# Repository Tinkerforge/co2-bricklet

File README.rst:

CO2 Bricklet
============

This repository contains the firmware source code and the hardware design
files. The documentation generator configs can be found at
https://github.com/Tinkerforge/generators

Repository Content
------------------

software/:
 * examples/: Examples for all supported languages
 * build/: Compiled files
 * src/: Source code of firmware
 * Makefile: Makefile to build project

hardware/:
 * Contains KiCad project files and additionally schematics as PDF

datasheets/:
 * Contains datasheets for sensors and complex ICs that are used

Hardware
--------

The hardware is designed with the open source EDA Suite KiCad
(http://www.kicad.org). Before you are able to open the files,
you have to install the Tinkerforge kicad-libraries
(https://github.com/Tinkerforge/kicad-libraries). You can either clone
them directly in hardware/ or clone them in a separate folder and
symlink them into hardware/
(ln -s kicad_path/kicad-libraries project_path/hardware). After that you
can open the .pro file in hardware/ with KiCad and from there view and
modify the schematics and the PCB layout.

Software
--------

If you want to do your own Brick/Bricklet firmware development we highly
recommend that you use our build environment setup script and read the
tutorial (https://www.tinkerforge.com/en/doc/Tutorials/Tutorial_Build_Environment/Tutorial.html).

To compile the C code we recommend you to install the newest GNU Arm Embedded
Toolchain (https://launchpad.net/gcc-arm-embedded/+download).
You also need to install bricklib (https://github.com/Tinkerforge/bricklib)
and brickletlib (https://github.com/Tinkerforge/brickletlib).

You can either clone it directly in software/src/ or clone it in a
separate folder and symlink it into software/src/
(ln -s bricklib_path/bricklib project_path/software/src/ and
ln -s brickletlib_path/brickletlib project_path/software/src/).
Finally make sure to have CMake installed
(http://www.cmake.org/cmake/resources/software.html).

After that you can build the firmware by invoking make in software/.
The firmware (.bin) can then be found in software/build/ and uploaded
with brickv (click button "Flashing" on start screen).

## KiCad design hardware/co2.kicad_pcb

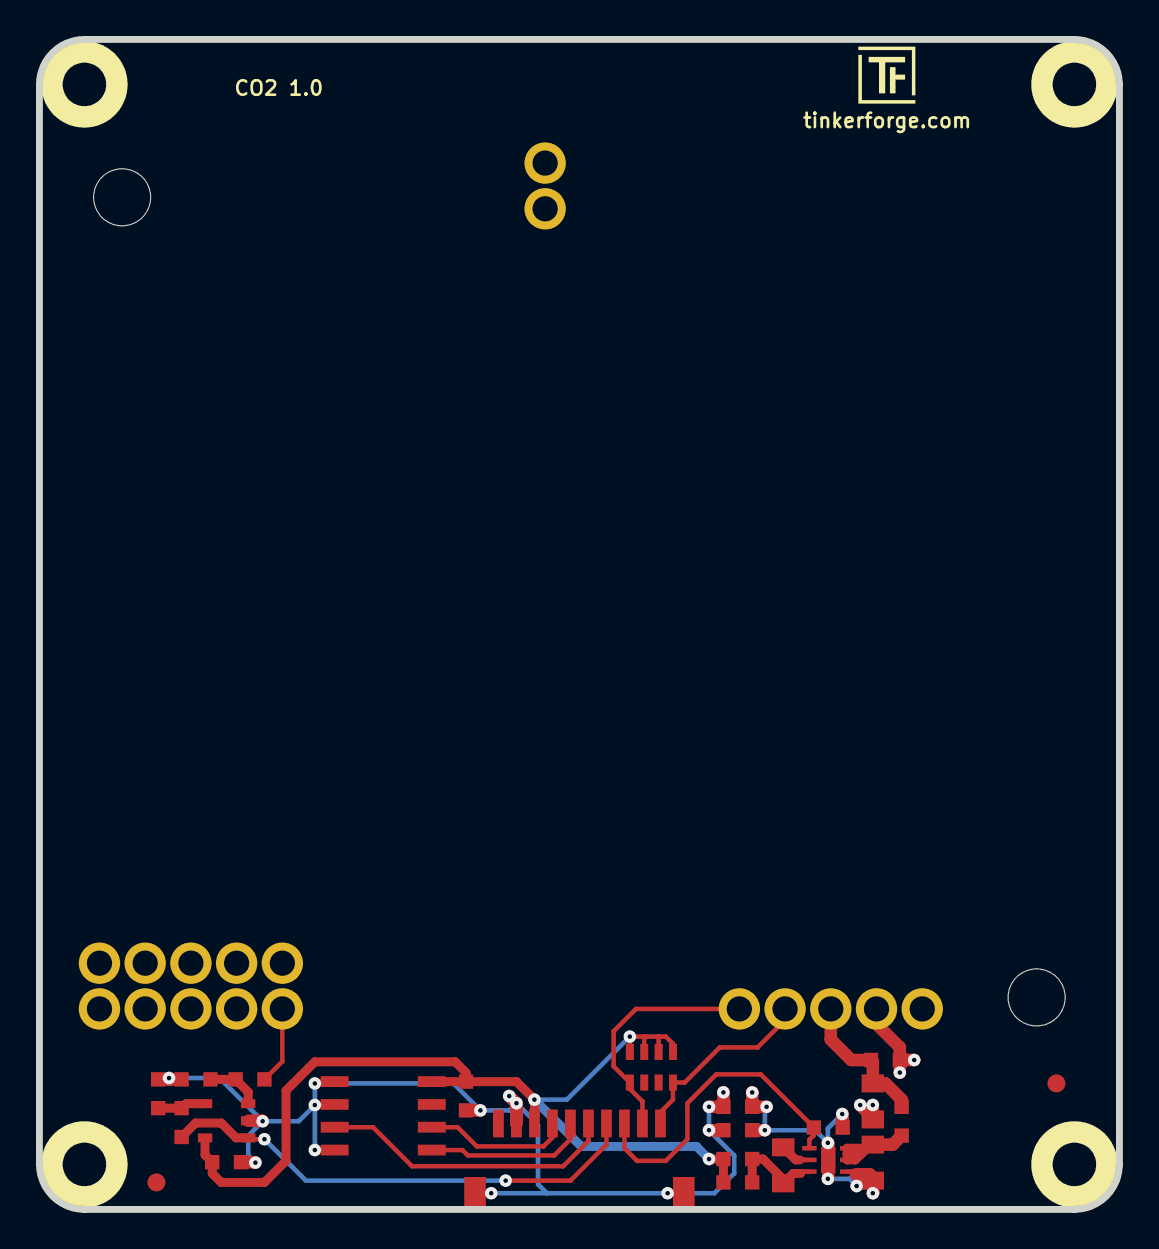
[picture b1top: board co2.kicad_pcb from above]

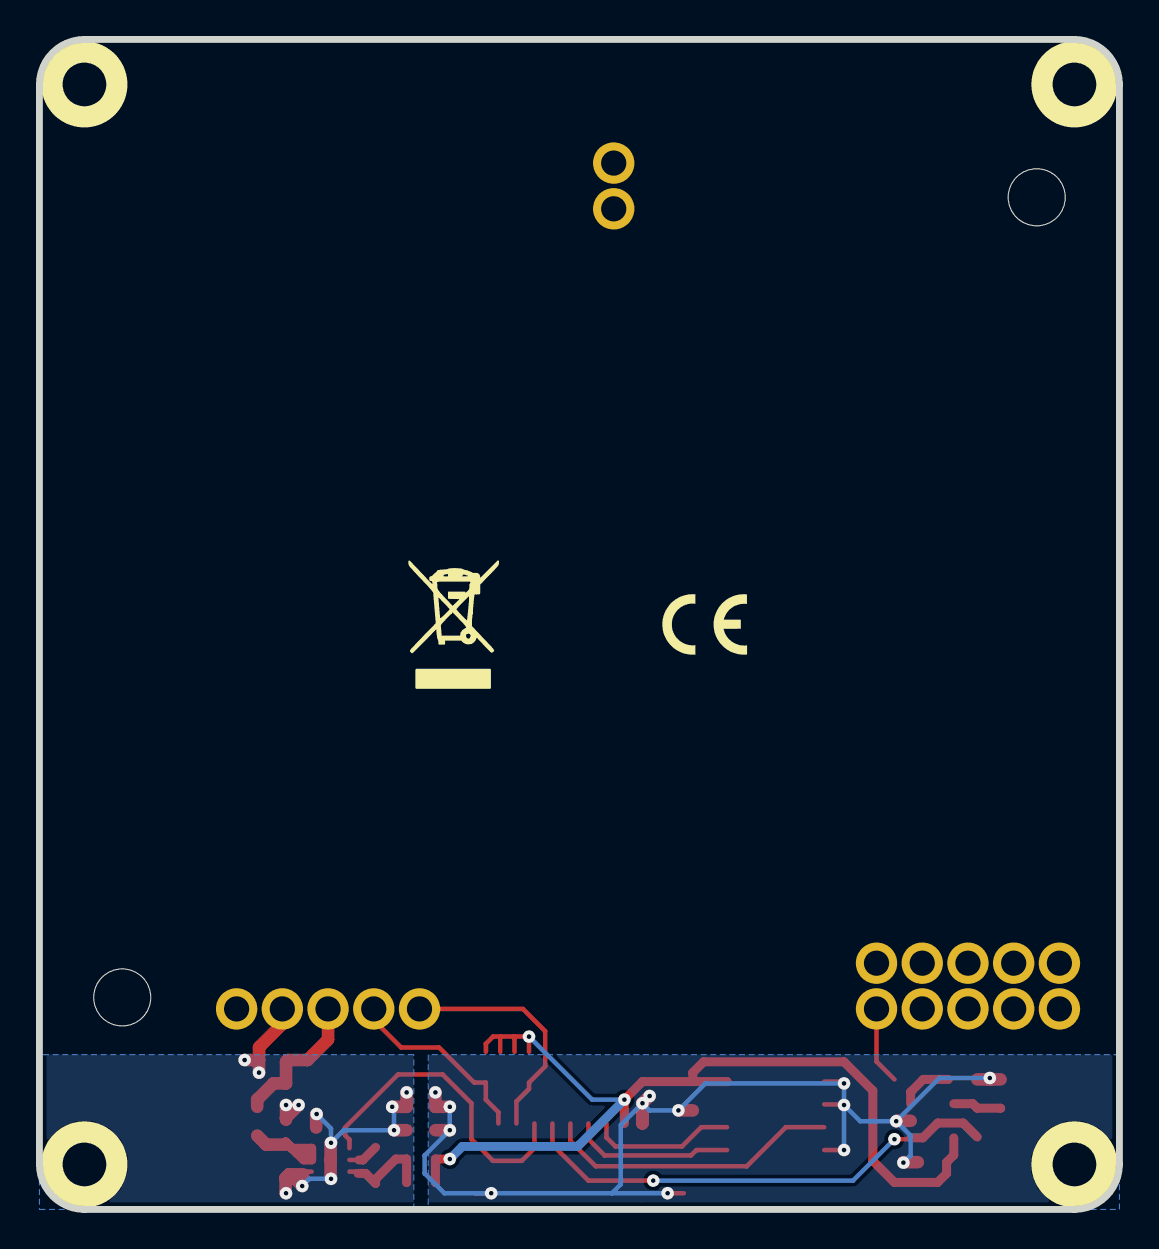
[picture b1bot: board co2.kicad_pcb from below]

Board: 2 copper layers, 60.0 x 65.0 mm, 30 parts (2 on the bottom side), 17 nets.

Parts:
C1, C2: 2.2µF; C0603
C3, C5, C7: 100nF; C0603
C4, C6: 4.7µF; C0805
Fiducial_Mark: VAL**; Fiducial_Mark
Fiducial_Mark#2: VAL**; Fiducial_Mark
L1, L4: INDUCT; C0603
L2: 0; C0603
L3: 1µH; C0805
P1: CON-SENSOR
R1: 10k; R0603
R2, R3: 3k; R0603
R4, R5: 3k9; R0603
RP1: 2k2; 4X0603
U1: M24C64; SOIC8
U2: FAN4860; UMLP_22
U3: TLV271; SOT23-5
U4: K30
U5, U6, U7, U8: DRILL; DRILL_NP
VAL: CE_5mm
VAL#2: WEEE_7mm_back; WEEE_7mm

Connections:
3V3: C1.1, C3.2, C5.2, L1.1, P1.3, RP1.1, RP1.2, RP1.3, RP1.4, U1.8, U3.5
+5V: C6.2, C7.2, L4.2, U4.3
AGND: C2.2, C4.2, C6.1, C7.1, L2.2, R1.2, U2.1, U2.EP, U4.2
EN: P1.8, R1.1, U2.4
GND: C1.2, C3.1, C5.1, L2.1, P1.2, P1.EP, R3.1, R4.1, U1.1, U1.2, U1.4, U3.2
unnamed: C2.1, L1.2, L3.1, U2.6
unnamed: C4.1, L4.1, U2.2, U2.3
unnamed: L3.2, U2.5
unnamed: P1.4, U1.6
unnamed: P1.5, U1.5
unnamed: P1.6, U1.3
unnamed: P1.7, R2.2, U3.1
unnamed: R2.1, R4.2, U3.4
unnamed: R3.2, R5.2, U3.3
unnamed: R5.1, U4.15
SCL: P1.10, RP1.5, U4.4
SDA: P1.9, RP1.8, U4.5

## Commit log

2015-05-18 Add initial stub implementation of CO2 Bricklet
2015-05-19 Add C examples
2015-05-19 Add C# examples
2015-05-19 Add Java examples
2015-05-19 Add JavaScript examples
2015-05-19 Add Perl examples
2015-05-19 Add PHP examples
2015-05-19 Add Python examples
2015-05-19 Add Ruby examples
2015-05-19 Add Shell examples
2015-05-19 Add VB.NET examples
2015-05-19 Add Matlab examples
2015-05-19 Add Mathematica examples
2015-05-19 prototype of co2 bricklet
2015-05-20 add configurable pin for co2 sensor config
2015-05-27 new co2 prototype with k30 sensor
2015-06-12 change gnd inductor to 0 ohm resistor
2015-06-18 Remove temporary file
2015-06-19 fix product name
2015-06-19 Add K30 i2c communication datasheet
2015-06-19 Add K30 Datasheet
2015-06-19 add configuration guide
2015-06-22 Add I2C configuration guide
2015-06-24 Fix version numbers
2015-06-24 Add .gitingore and toolchain files
2015-06-24 Fix device identifier
2015-06-24 Add LabVIEW examples
    Also clean up other examples.
2015-06-24 update guide
2015-06-25 Fix typos in Octave examples
2015-07-06 Add I2C communication with sensor
2015-07-08 MATLAB example fix
2015-07-23 Make JavaScript browser example textarea readonly
2015-07-27 Cleanup C/C++, C#, Java, Python and Ruby examples
2015-07-29 Reformat changelog
2015-08-07 Use full device class name in Python examples
2015-08-12 Fix minor warnings in C/C++ examples
2015-08-13 Use correct simple value type
2015-08-14 Add Delphi examples
2015-08-18 Cleanup VB.NET examples
2015-08-19 Cleanup Perl examples
2015-08-20 Fix range type in Java example
2015-08-21 Use short print statement in Perl example
2015-09-10 Duplicate cmake call to fix bug during cmake creation
    Also, toolchain is now in bricklib.
2015-09-30 Generator based example cleanup
2015-10-20 drc check
2015-10-26 Add error detection (untested)
    * API for error counters is still missing
2015-11-12 matlab: Fix callback handling for R2014a
    http://undocumentedmatlab.com/blog/matlab-callbacks-for-java-events-in-r2014a
2015-11-25 Include date and commit into changelog
2015-11-30 vbnet: Break long line
2015-12-15 Only get value every 2s, sleep 20ms through tick
2016-01-05 Use different state machine for better timing
2016-01-06 add pdf schematic, fix library settings
2016-01-07 Remove WIP marker
2016-01-11 Update changelog
2016-01-11 Fix typo
2016-05-18 c: Add missing device destroy call
2016-06-29 Whitespace
2016-07-01 Make the change UID comment more explicit
2017-04-13 csharp: Adapt example
2017-04-21 shell: Adapt example
2017-06-02 octave: Use javaObject instead of deprecated java_new
2017-11-30 Update examples from generator
2017-12-07 mathematica: Also generate .nb files
2018-01-26 c: Fine-tune printf format
2018-02-02 Update examples
2018-02-19 javascript: Close div tag correctly
2018-02-20 Cleanup KiCad libraries config
    Ensure LibDir=kicad-libraries and LibName1=tinkerforge.
    Remove special library.
2018-03-28 Add 3d information (final)
2018-03-28 Add 3d models (*.FCStd & *.step)
2018-05-24 perl: Use strict in examples
2018-07-11 Add Makefile with docker support
2018-07-11 Update directory structure and build instructions
2018-07-11 Remove obsolete generate_makefile scripts
2018-09-14 vbnet: Fix typo in comment
2018-11-06 Add rust examples
2018-11-07 rust: Accept host names for ip connection, fix naming inconsistencies
2018-11-07 rust: Rename callback receivers.
2018-12-14 Add go examples.
2018-12-18 go: Change import path.
2018-12-18 go: Change import path again.
2018-12-20 rust: Reformat examples.
2019-01-24 mqtt: Add examples.
2019-01-24 mqtt: Fix example header.
2019-01-24 mqtt: Remove executable bit in example permissions.
2019-01-24 go: Minor example fixes.
2019-01-24 mqtt: Minor example fixes.
2019-03-28 mqtt: Fix whitespace.
2019-08-22 c: Adapt to bindings changes
2020-01-13 examples: Use python3 input instead of python2 raw_input.
2020-01-13 examples: mqtt: Remove trailing whitespace.
2021-10-25 Update KiCad link
    https://www.kicad.org/blog/2021/10/Avoid-links-to-former-kicad-domain/
2022-05-10 go: Fix format string
2022-07-06 Add license files.

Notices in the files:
hardware/co2.kicad_pcb:
Licensed under CERN OHL v.1.1
Copyright (©) 2015, B.Nordmeyer
